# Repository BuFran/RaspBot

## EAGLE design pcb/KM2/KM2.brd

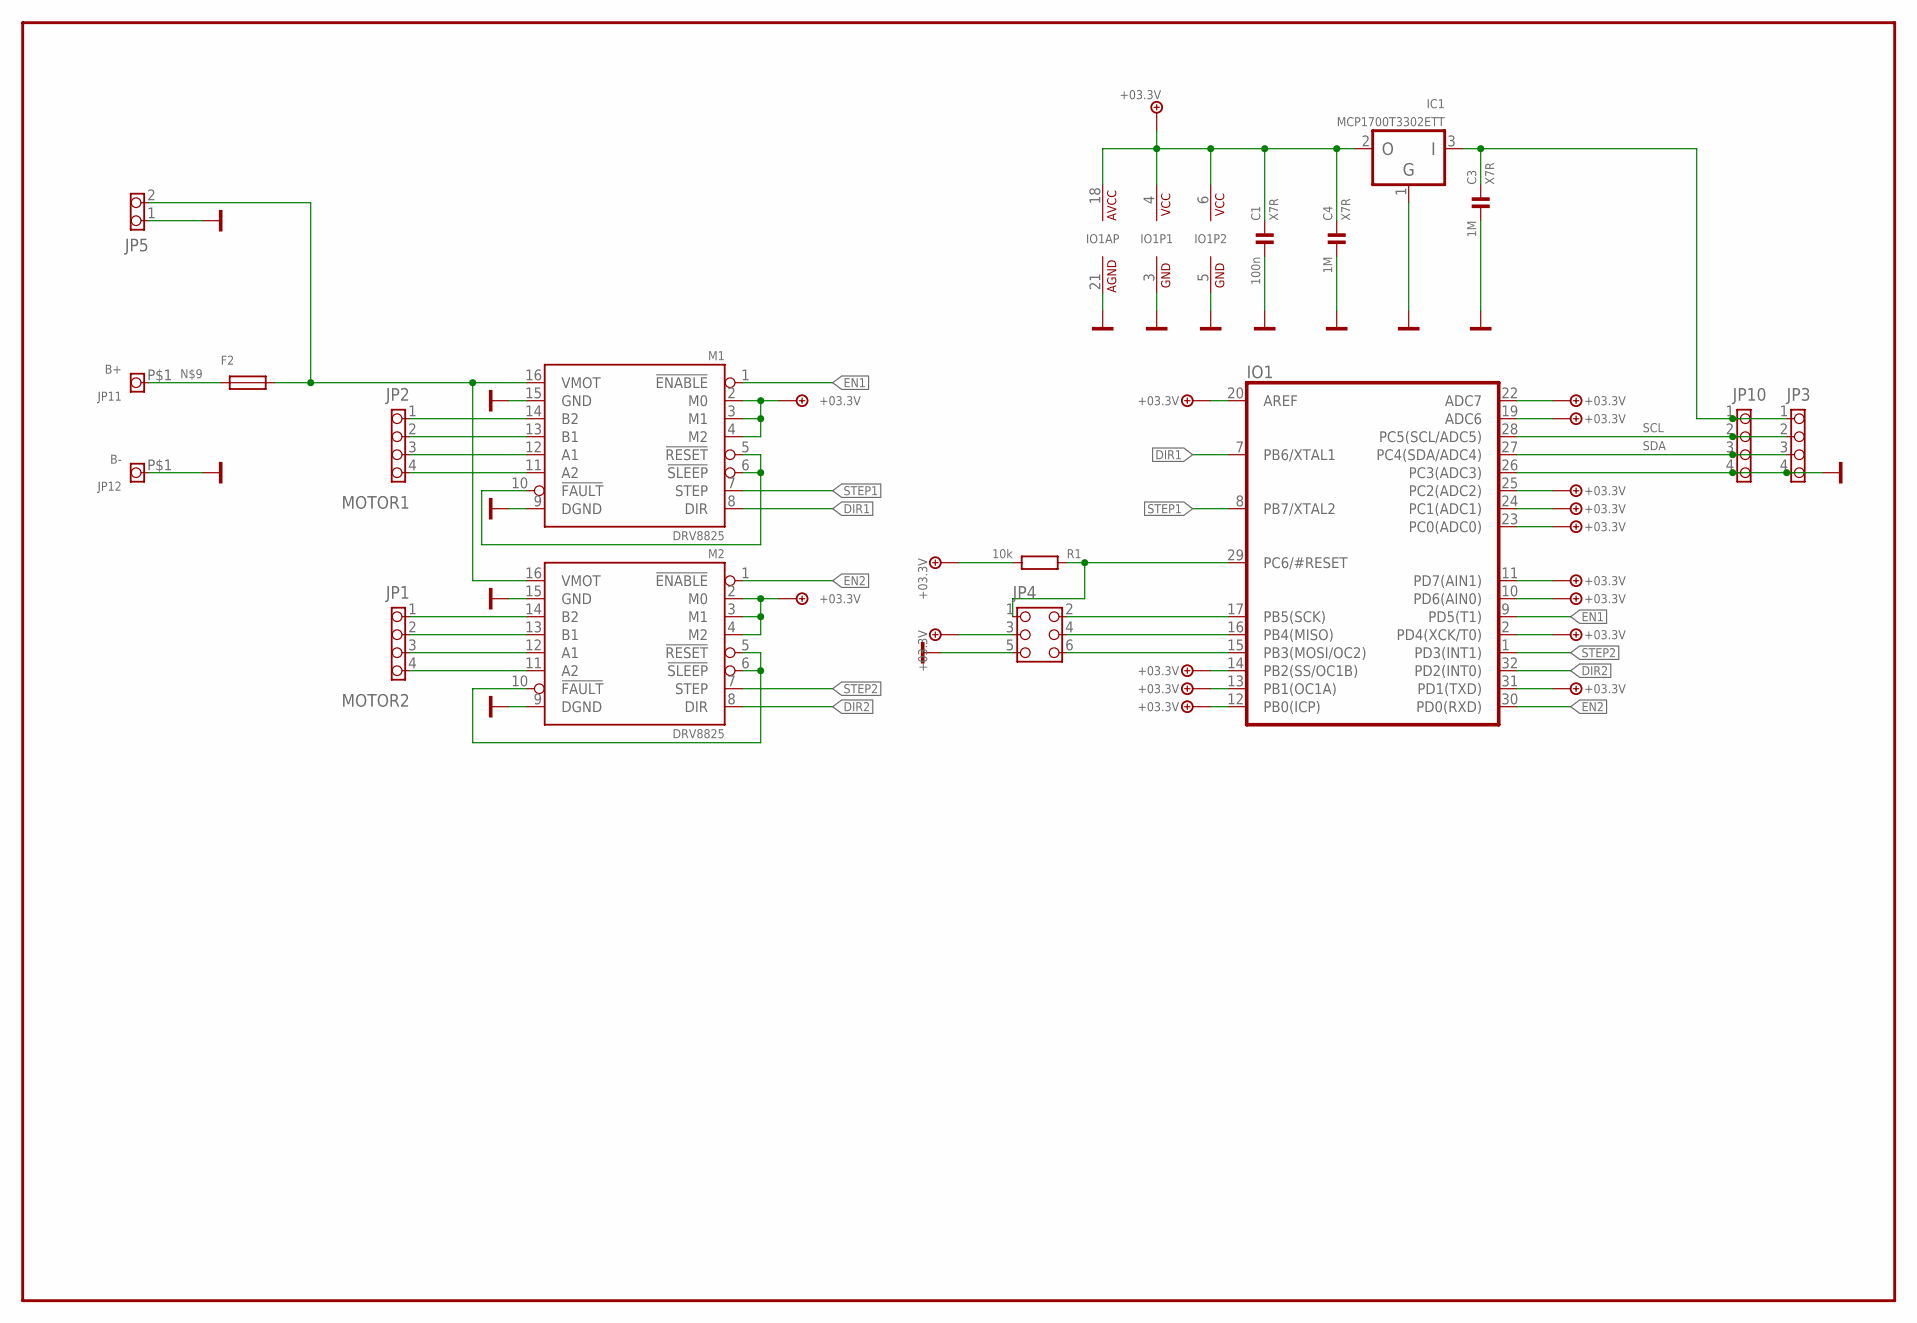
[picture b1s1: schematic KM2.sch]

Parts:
C1: 100n; 0805
C3, C4: 1M; 0805
F2: F_1812; 1812
IC1: MCP1700T3302ETT; SOT23
IO1: MEGA8; TQFP32
JP1: MOTOR2; 1X04_254_EDGE
JP2: MOTOR1; 1X04_254_EDGE
JP3, JP10: PINHD-1X4_250_MX5267; 1X04_250_MX5267
JP4: PINHD-2X3_254_FP; 2X03_254_FP
JP5: PINHD-1X2_250_MX5267; 1X02_250_MX5267
JP11: B+; 1X01_254_254_PAD
JP12: B-; 1X01_254_254_PAD
M1, M2: DRV8825; MODULE_16P
R1: 10k; 0805

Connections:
+3.3V: C1.1, C4.1, IC1.2 (OUT), IO1.2 (PD4(XCK/T0)), IO1.4 (VCC), IO1.6 (VCC), IO1.10 (PD6(AIN0)), IO1.11 (PD7(AIN1)), IO1.12 (PB0(ICP)), IO1.13 (PB1(OC1A)), IO1.14 (PB2(SS/OC1B)), IO1.18 (VCC), IO1.19 (ADC6), IO1.20 (AREF), IO1.22 (ADC7), IO1.23 (PC0(ADC0)), IO1.24 (PC1(ADC1)), IO1.25 (PC2(ADC2)), IO1.31 (PD1(TXD)), JP4.3, M1.2 (M0), M1.3 (M1), M1.4 (M2), M2.2 (M0), M2.3 (M1), M2.4 (M2), R1.1
DIR1: IO1.7 (PB6/XTAL1), M1.8 (DIR)
DIR2: IO1.32 (PD2(INT0)), M2.8 (DIR)
EN1: IO1.9 (PD5(T1)), M1.1 (!ENABLE)
EN2: IO1.30 (PD0(RXD)), M2.1 (!ENABLE)
GND: C1.2, C3.2, C4.2, IC1.1 (GND), IO1.3 (GND), IO1.5 (GND), IO1.21 (GND), IO1.26 (PC3(ADC3)), JP3.4, JP4.5, JP5.1, JP10.4, JP12.P$1, M1.9 (DGND), M1.15 (GND), M2.9 (DGND), M2.15 (GND)
unnamed: JP1.1, M2.14 (B2)
unnamed: JP1.2, M2.13 (B1)
unnamed: JP1.3, M2.12 (A1)
unnamed: JP1.4, M2.11 (A2)
unnamed: JP2.1, M1.14 (B2)
unnamed: JP2.2, M1.13 (B1)
unnamed: JP2.3, M1.12 (A1)
unnamed: JP2.4, M1.11 (A2)
unnamed: F2.1, JP11.P$1
unnamed: IO1.17 (PB5(SCK)), JP4.2
unnamed: IO1.16 (PB4(MISO)), JP4.4
unnamed: M2.5 (!RESET), M2.6 (!SLEEP), M2.10 (!FAULT)
unnamed: M1.5 (!RESET), M1.6 (!SLEEP), M1.10 (!FAULT)
unnamed: C3.1, IC1.3 (IN), JP3.1, JP10.1
unnamed: IO1.15 (PB3(MOSI/OC2)), JP4.6
unnamed: IO1.29 (PC6/#RESET), JP4.1, R1.2
SCL: IO1.28 (PC5(SCL/ADC5)), JP3.2, JP10.2
SDA: IO1.27 (PC4(SDA/ADC4)), JP3.3, JP10.3
STEP1: IO1.8 (PB7/XTAL2), M1.7 (STEP)
STEP2: IO1.1 (PD3(INT1)), M2.7 (STEP)
VBAT+: F2.2, JP5.2, M1.16 (VMOT), M2.16 (VMOT)

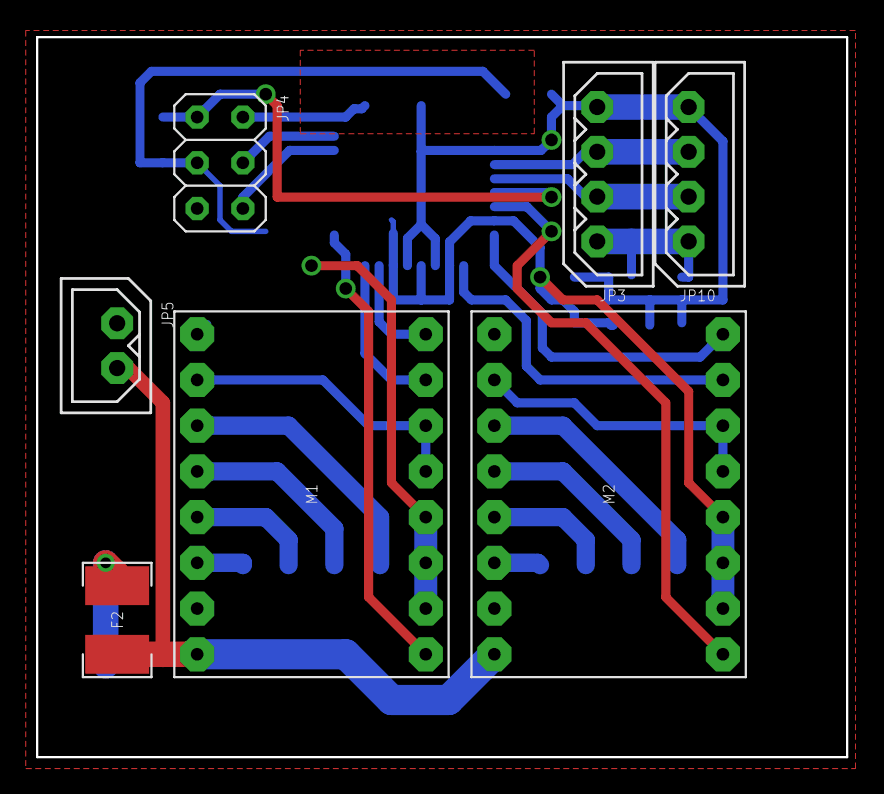
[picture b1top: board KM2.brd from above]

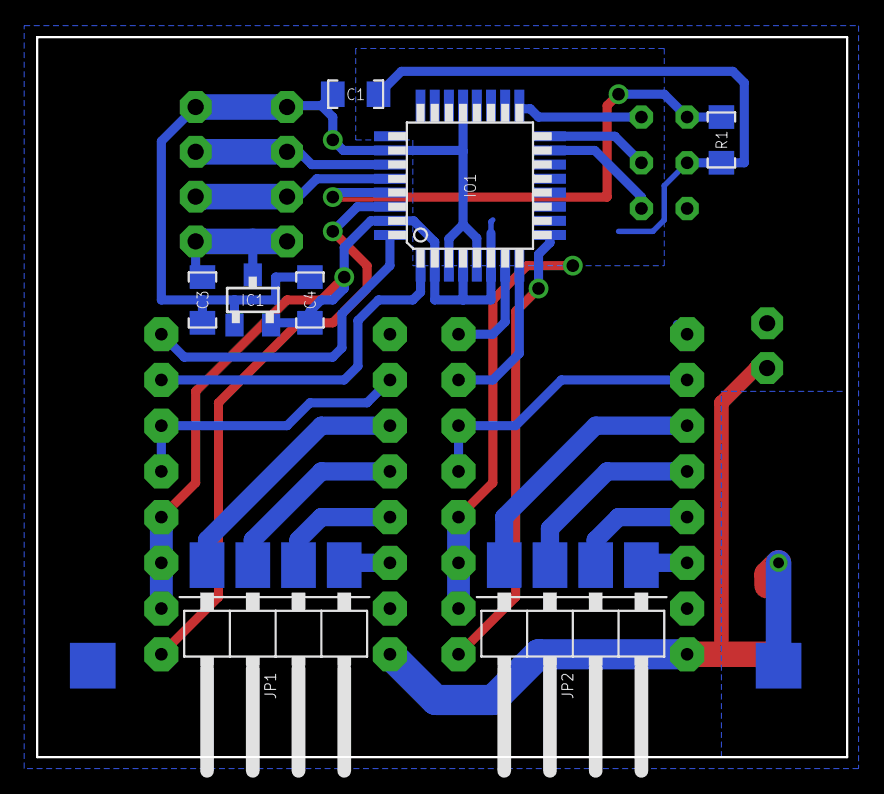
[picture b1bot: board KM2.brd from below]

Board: 2 copper layers, 45.0 x 40.0 mm, 19 parts (10 on the bottom side), 27 nets.

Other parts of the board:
U$2: DIN_DOCFIELD_SCALE2
U$3: DIN_A4_SCALE2

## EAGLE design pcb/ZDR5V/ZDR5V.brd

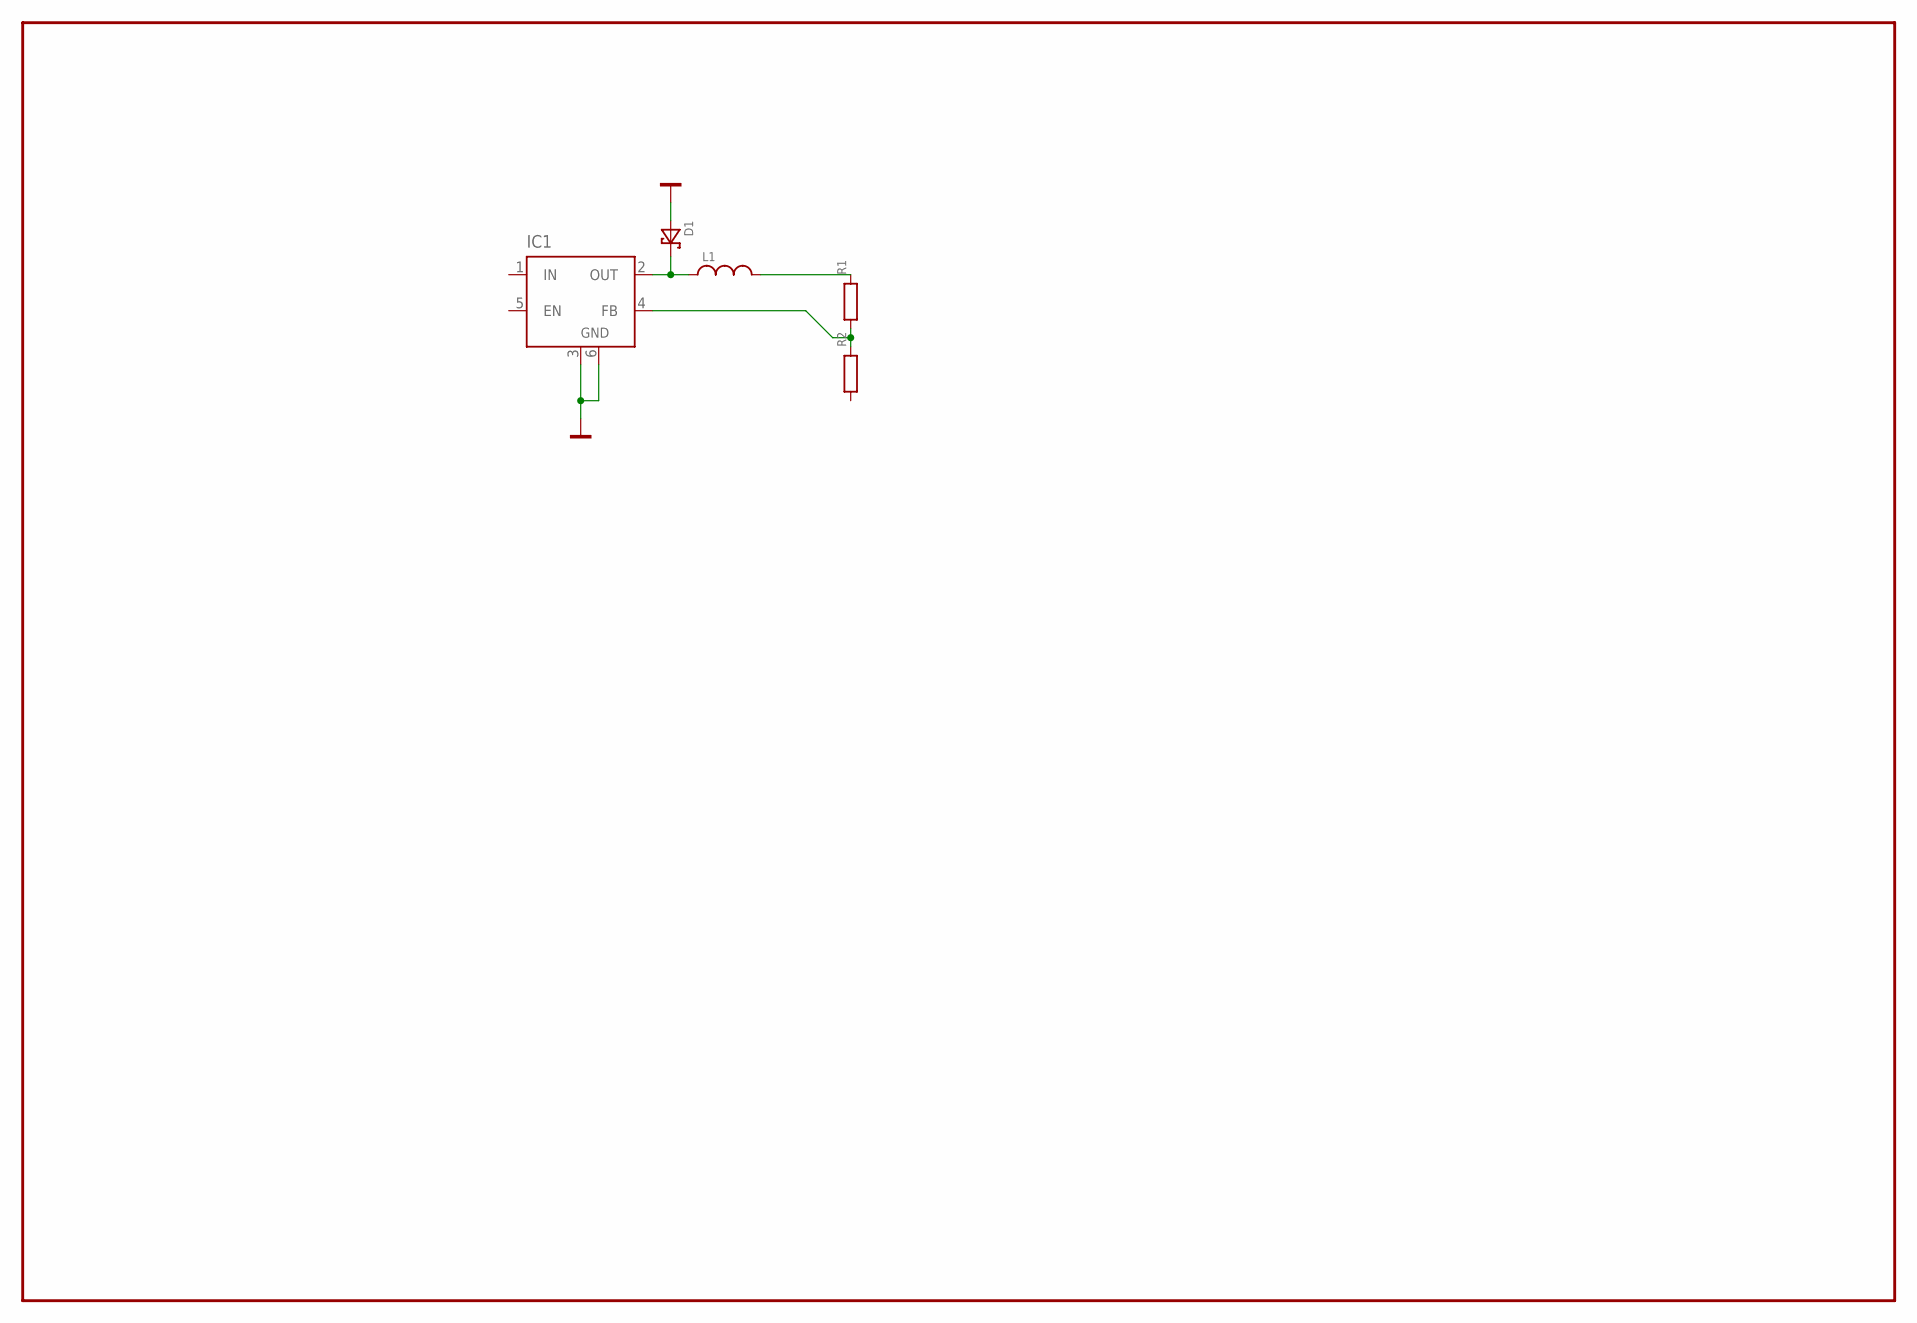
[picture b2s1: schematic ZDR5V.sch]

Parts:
D1: D_SCHOTKY_SMB; D_SMB
IC1: LM2596S; TO263-5
L1: L_DE1209; DE1209
R1, R2: R_R0805; 0805

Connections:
GND: D1.A, IC1.3 (GND), IC1.6 (GND)
unnamed: D1.K, IC1.2 (OUT), L1.2
unnamed: L1.1, R1.2
unnamed: IC1.4 (FB), R1.1, R2.2

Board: 2 copper layers, 7 parts (5 on the bottom side), 4 nets, no tracks yet.

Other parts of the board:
U$1: DIN_A4_SCALE2
U$2: DIN_DOCFIELD_SCALE2

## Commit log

2016-10-11 ZDR5V
2016-10-11 [MNDP] next work
2016-10-11 mndp
2016-10-11 km2 edits FINAL!!
